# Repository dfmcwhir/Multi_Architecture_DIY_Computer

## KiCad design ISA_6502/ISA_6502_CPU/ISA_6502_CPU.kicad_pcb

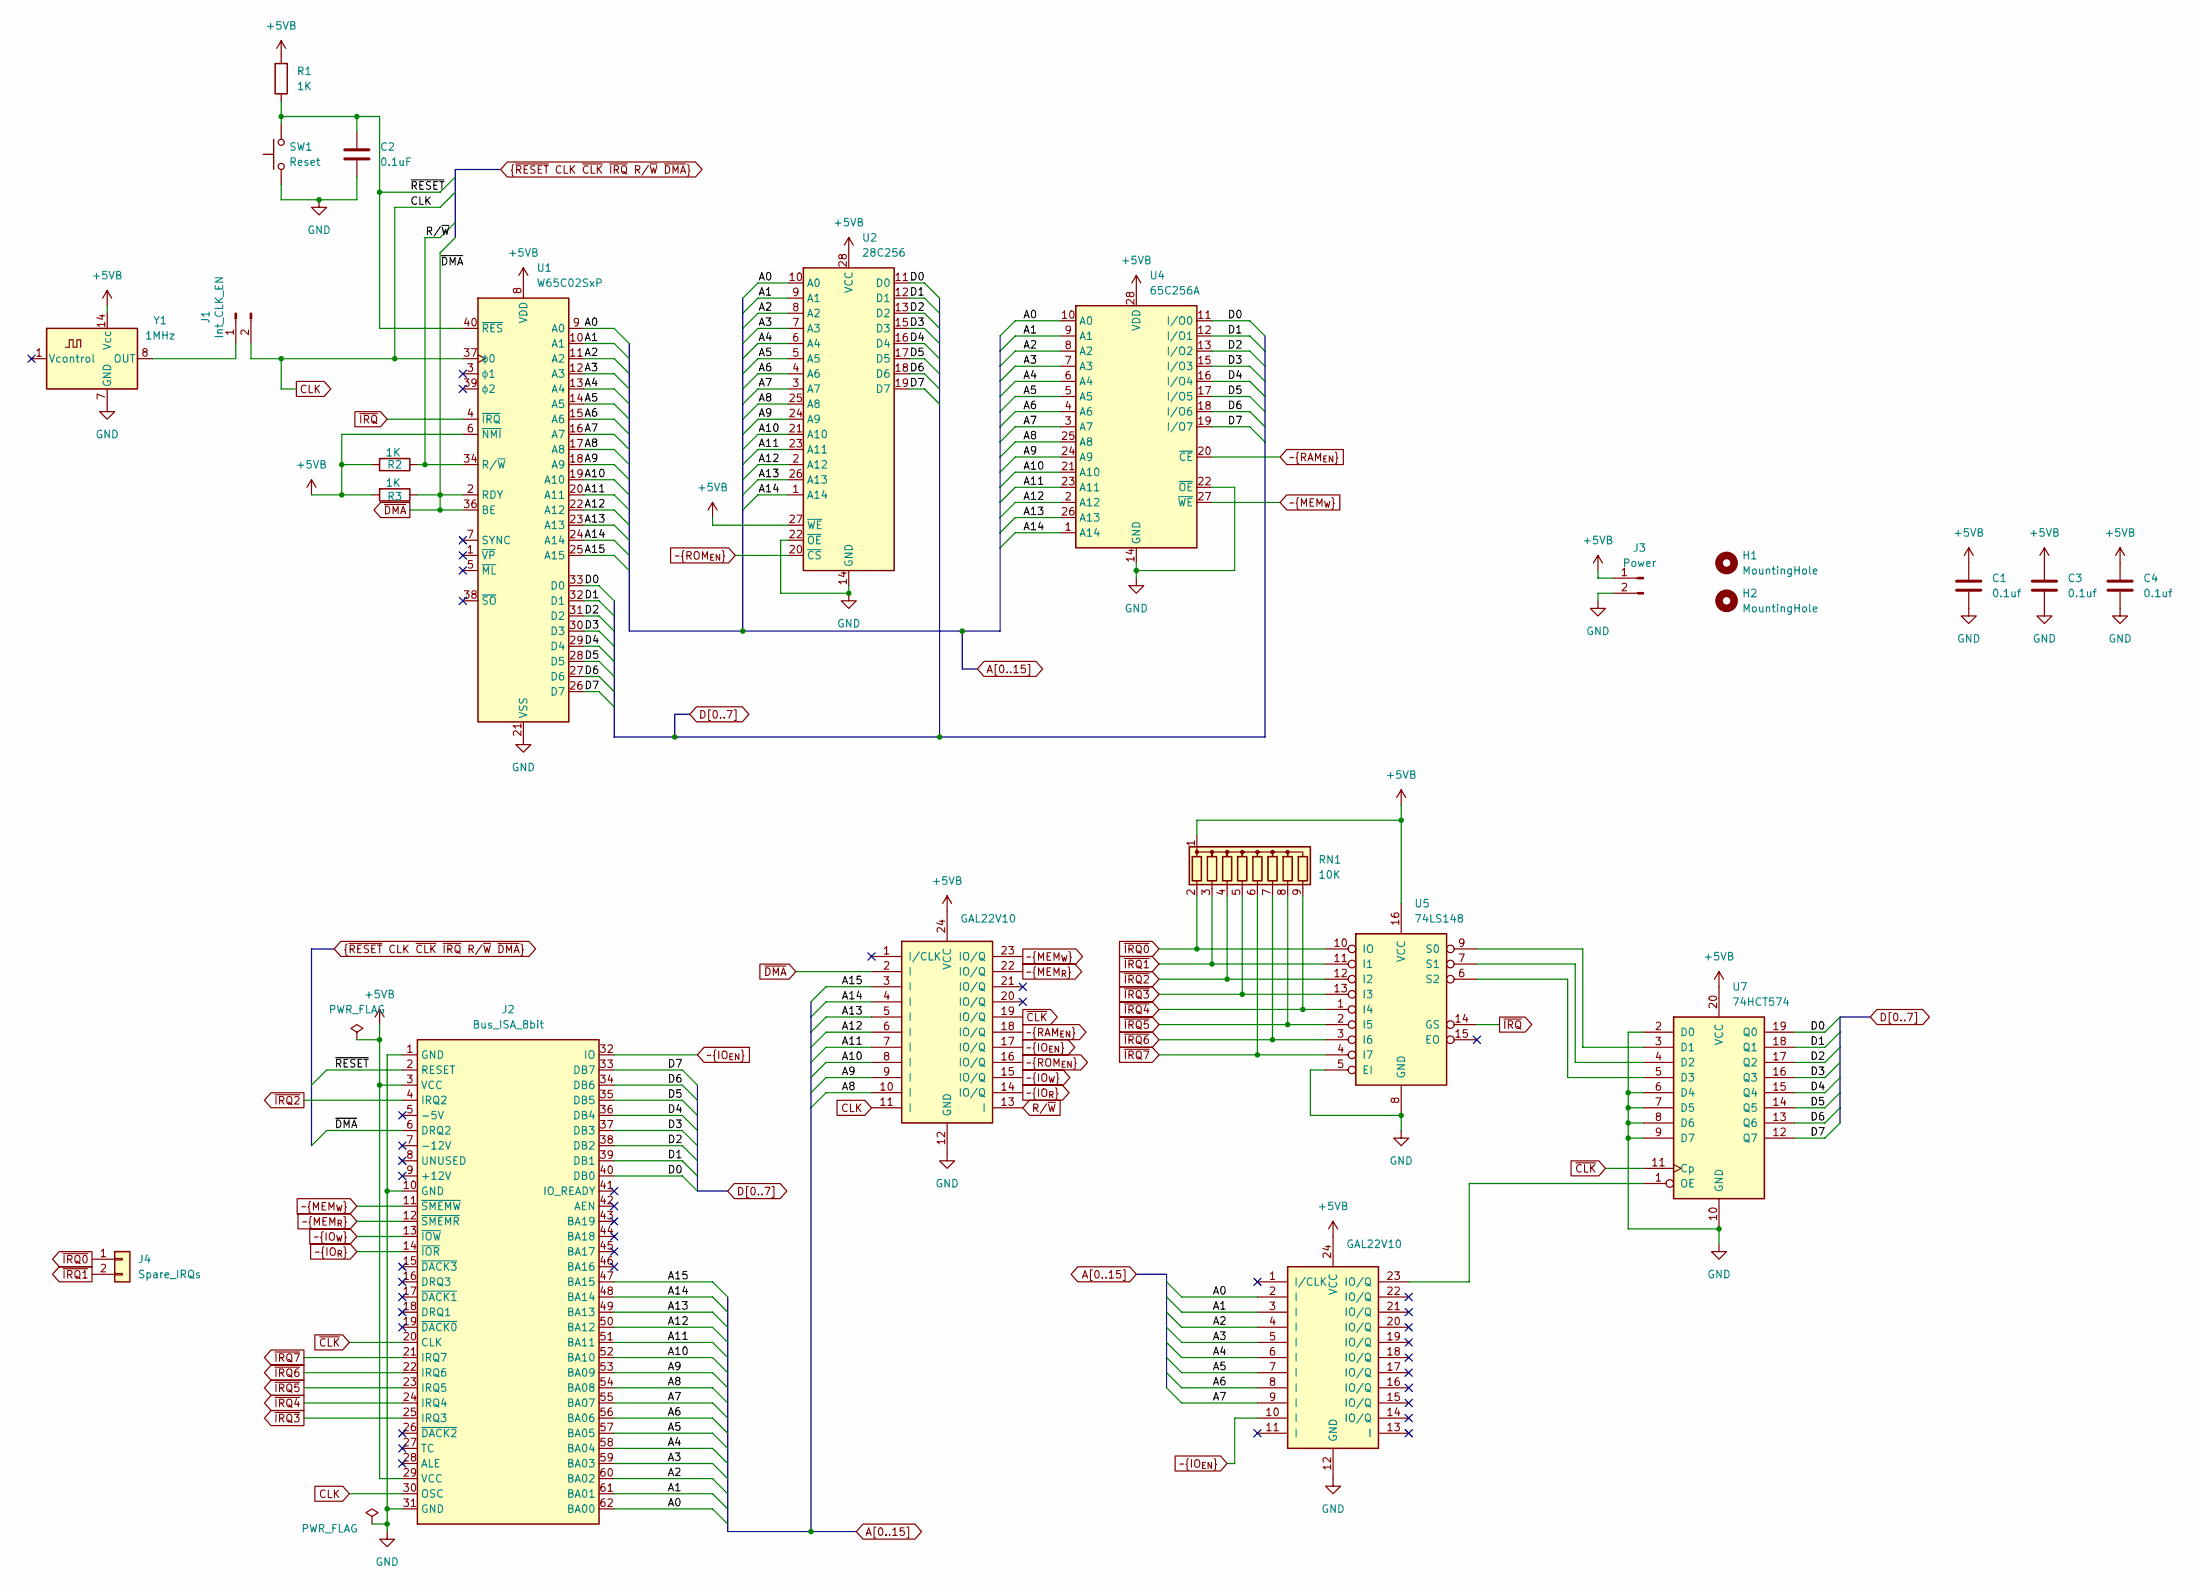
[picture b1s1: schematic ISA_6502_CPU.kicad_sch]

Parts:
C1, C3, C4: 0.1uf; C_Disc_D4.7mm_W2.5mm_P5.00mm
C2: 0.1uF; C_Disc_D4.7mm_W2.5mm_P5.00mm
H1, H2: MountingHole; MountingHole_3.2mm_M3
J1: Int_CLK_EN; PinHeader_1x02_P2.54mm_Vertical
J2: Bus_ISA_8bit; BUS_8-bit_ISA
J3: Power; PinHeader_1x02_P2.54mm_Vertical
J4: Spare_IRQs; PinHeader_1x02_P2.54mm_Vertical
R1, R2, R3: 1K; R_Axial_DIN0207_L6.3mm_D2.5mm_P10.16mm_Horizontal
RN1: 10K; R_Array_SIP9
SW1: Reset; SW_PUSH_6mm
U1: W65C02SxP; DIP-40_W15.24mm
U2: 28C256; DIP-28_W15.24mm
U3, U6: GAL22V10; DIP-24_W7.62mm
U4: 65C256A; DIP-28_W15.24mm
U5: 74LS148; DIP-16_W7.62mm
U7: 74HCT574; DIP-20_W7.62mm
Y1: 1MHz; Oscillator_DIP-14

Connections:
+5VB: C1.1, C3.1, C4.1, J2.3 (VCC), J2.29 (VCC), J3.1, R1.2, R2.2, R3.2, RN1.1 (common), U1.6 (~NMI), U1.8 (VDD), U2.27 (~WE), U2.28 (VCC), U3.24 (VCC), U4.28 (VDD), U5.16 (VCC), U6.24 (VCC), U7.20 (VCC), Y1.14 (Vcc)
A0: J2.62 (BA00), U1.9 (A0), U2.10 (A0), U4.10 (A0), U6.2 (I)
A1: J2.61 (BA01), U1.10 (A1), U2.9 (A1), U4.9 (A1), U6.3 (I)
A2: J2.60 (BA02), U1.11 (A2), U2.8 (A2), U4.8 (A2), U6.4 (I)
A3: J2.59 (BA03), U1.12 (A3), U2.7 (A3), U4.7 (A3), U6.5 (I)
A4: J2.58 (BA04), U1.13 (A4), U2.6 (A4), U4.6 (A4), U6.6 (I)
A5: J2.57 (BA05), U1.14 (A5), U2.5 (A5), U4.5 (A5), U6.7 (I)
A6: J2.56 (BA06), U1.15 (A6), U2.4 (A6), U4.4 (A6), U6.8 (I)
A7: J2.55 (BA07), U1.16 (A7), U2.3 (A7), U4.3 (A7), U6.9 (I)
A8: J2.54 (BA08), U1.17 (A8), U2.25 (A8), U3.10 (I), U4.25 (A8)
A9: J2.53 (BA09), U1.18 (A9), U2.24 (A9), U3.9 (I), U4.24 (A9)
A10: J2.52 (BA10), U1.19 (A10), U2.21 (A10), U3.8 (I), U4.21 (A10)
A11: J2.51 (BA11), U1.20 (A11), U2.23 (A11), U3.7 (I), U4.23 (A11)
A12: J2.50 (BA12), U1.22 (A12), U2.2 (A12), U3.6 (I), U4.2 (A12)
A13: J2.49 (BA13), U1.23 (A13), U2.26 (A13), U3.5 (I), U4.26 (A13)
A14: J2.48 (BA14), U1.24 (A14), U2.1 (A14), U3.4 (I), U4.1 (A14)
A15: J2.47 (BA15), U1.25 (A15), U3.3 (I)
CLK: J1.2, J2.30 (OSC), U1.37 (ϕ0), U3.11 (I)
D0: J2.40 (DB0), U1.33 (D0), U2.11 (D0), U4.11 (I/O0), U7.19 (Q0)
D1: J2.39 (DB1), U1.32 (D1), U2.12 (D1), U4.12 (I/O1), U7.18 (Q1)
D2: J2.38 (DB2), U1.31 (D2), U2.13 (D2), U4.13 (I/O2), U7.17 (Q2)
D3: J2.37 (DB3), U1.30 (D3), U2.15 (D3), U4.15 (I/O3), U7.16 (Q3)
D4: J2.36 (DB4), U1.29 (D4), U2.16 (D4), U4.16 (I/O4), U7.15 (Q4)
D5: J2.35 (DB5), U1.28 (D5), U2.17 (D5), U4.17 (I/O5), U7.14 (Q5)
D6: J2.34 (DB6), U1.27 (D6), U2.18 (D6), U4.18 (I/O6), U7.13 (Q6)
D7: J2.33 (DB7), U1.26 (D7), U2.19 (D7), U4.19 (I/O7), U7.12 (Q7)
GND: C1.2, C2.2, C3.2, C4.2, J2.1 (GND), J2.10 (GND), J2.31 (GND), J3.2, SW1.1, U1.21 (VSS), U2.14 (GND), U2.22 (~OE), U3.12 (GND), U4.14 (GND), U4.22 (~OE), U5.5 (EI), U5.8 (GND), U6.12 (GND), U7.2 (D0), U7.6 (D4), U7.7 (D5), U7.8 (D6), U7.9 (D7), U7.10 (GND), Y1.7 (GND)
unnamed: J1.1, Y1.8 (OUT)
unnamed: U5.9 (S0), U7.3 (D1)
unnamed: U5.7 (S1), U7.4 (D2)
unnamed: U5.6 (S2), U7.5 (D3)
unnamed: U6.23 (IO/Q), U7.1 (OE)
R/~W: R2.1, U1.34 (R/~W), U3.13 (I)
~CLK: J2.20 (CLK), U3.19 (IO/Q), U7.11 (Cp)
~DMA: J2.6 (DRQ2), R3.1, U1.2 (RDY), U1.36 (BE), U3.2 (I)
~IO_{EN}: J2.32 (IO), U3.17 (IO/Q), U6.10 (I)
~IO_{R}: J2.14 (~IOR), U3.14 (IO/Q)
~IO_{W}: J2.13 (~IOW), U3.15 (IO/Q)
~IRQ0: J4.1, RN1.2 (R1), U5.10 (IO)
~IRQ1: J4.2, RN1.3 (R2), U5.11 (I1)
~IRQ2: J2.4 (IRQ2), RN1.4 (R3), U5.12 (I2)
~IRQ3: J2.25 (IRQ3), RN1.5 (R4), U5.13 (I3)
~IRQ4: J2.24 (IRQ4), RN1.9 (R8), U5.1 (I4)
~IRQ5: J2.23 (IRQ5), RN1.8 (R7), U5.2 (I5)
~IRQ6: J2.22 (IRQ6), RN1.7 (R6), U5.3 (I6)
~IRQ7: J2.21 (IRQ7), RN1.6 (R5), U5.4 (I7)
~IRQ: U1.4 (~IRQ), U5.14 (GS)
~MEM_{R}: J2.12 (~SMEMR), U3.22 (IO/Q)
~MEM_{W}: J2.11 (~SMEMW), U3.23 (IO/Q), U4.27 (~WE)
~RAM_{EN}: U3.18 (IO/Q), U4.20 (~CE)
~RESET: C2.1, J2.2 (RESET), R1.1, SW1.2, U1.40 (~RES)
~ROM_{EN}: U2.20 (~CS), U3.16 (IO/Q)

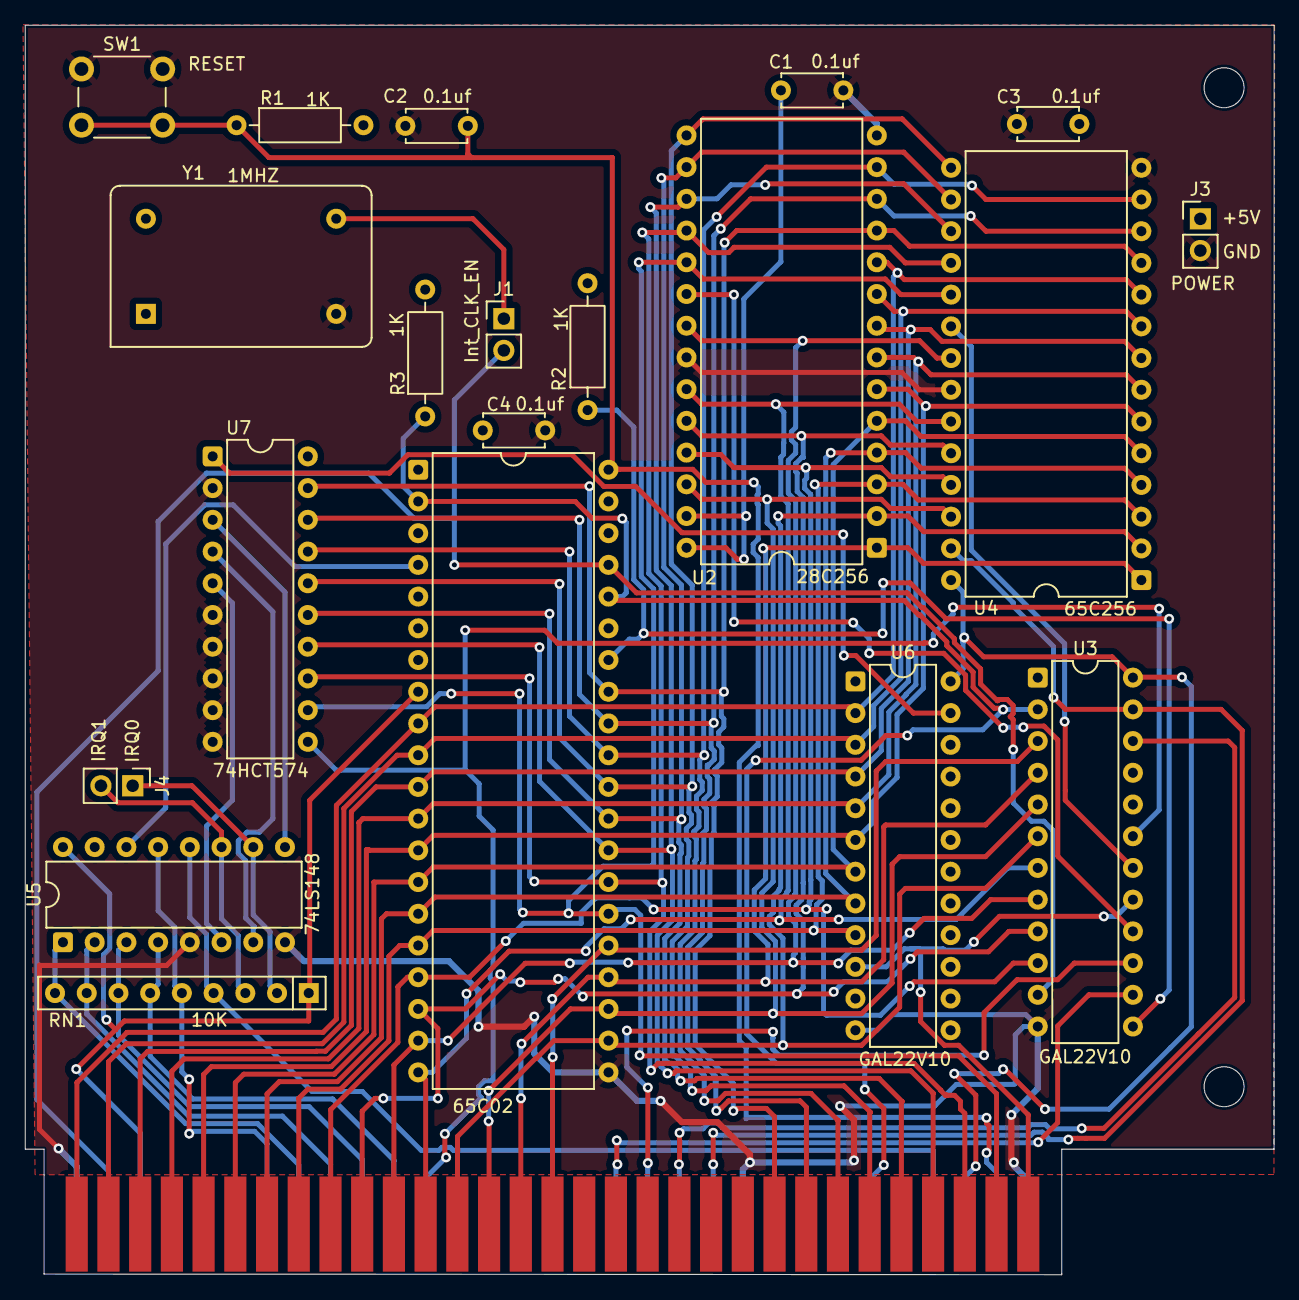
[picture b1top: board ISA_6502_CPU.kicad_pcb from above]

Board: 2 copper layers, 100.0 x 100.1 mm, 23 parts (0 on the bottom side), 52 nets.

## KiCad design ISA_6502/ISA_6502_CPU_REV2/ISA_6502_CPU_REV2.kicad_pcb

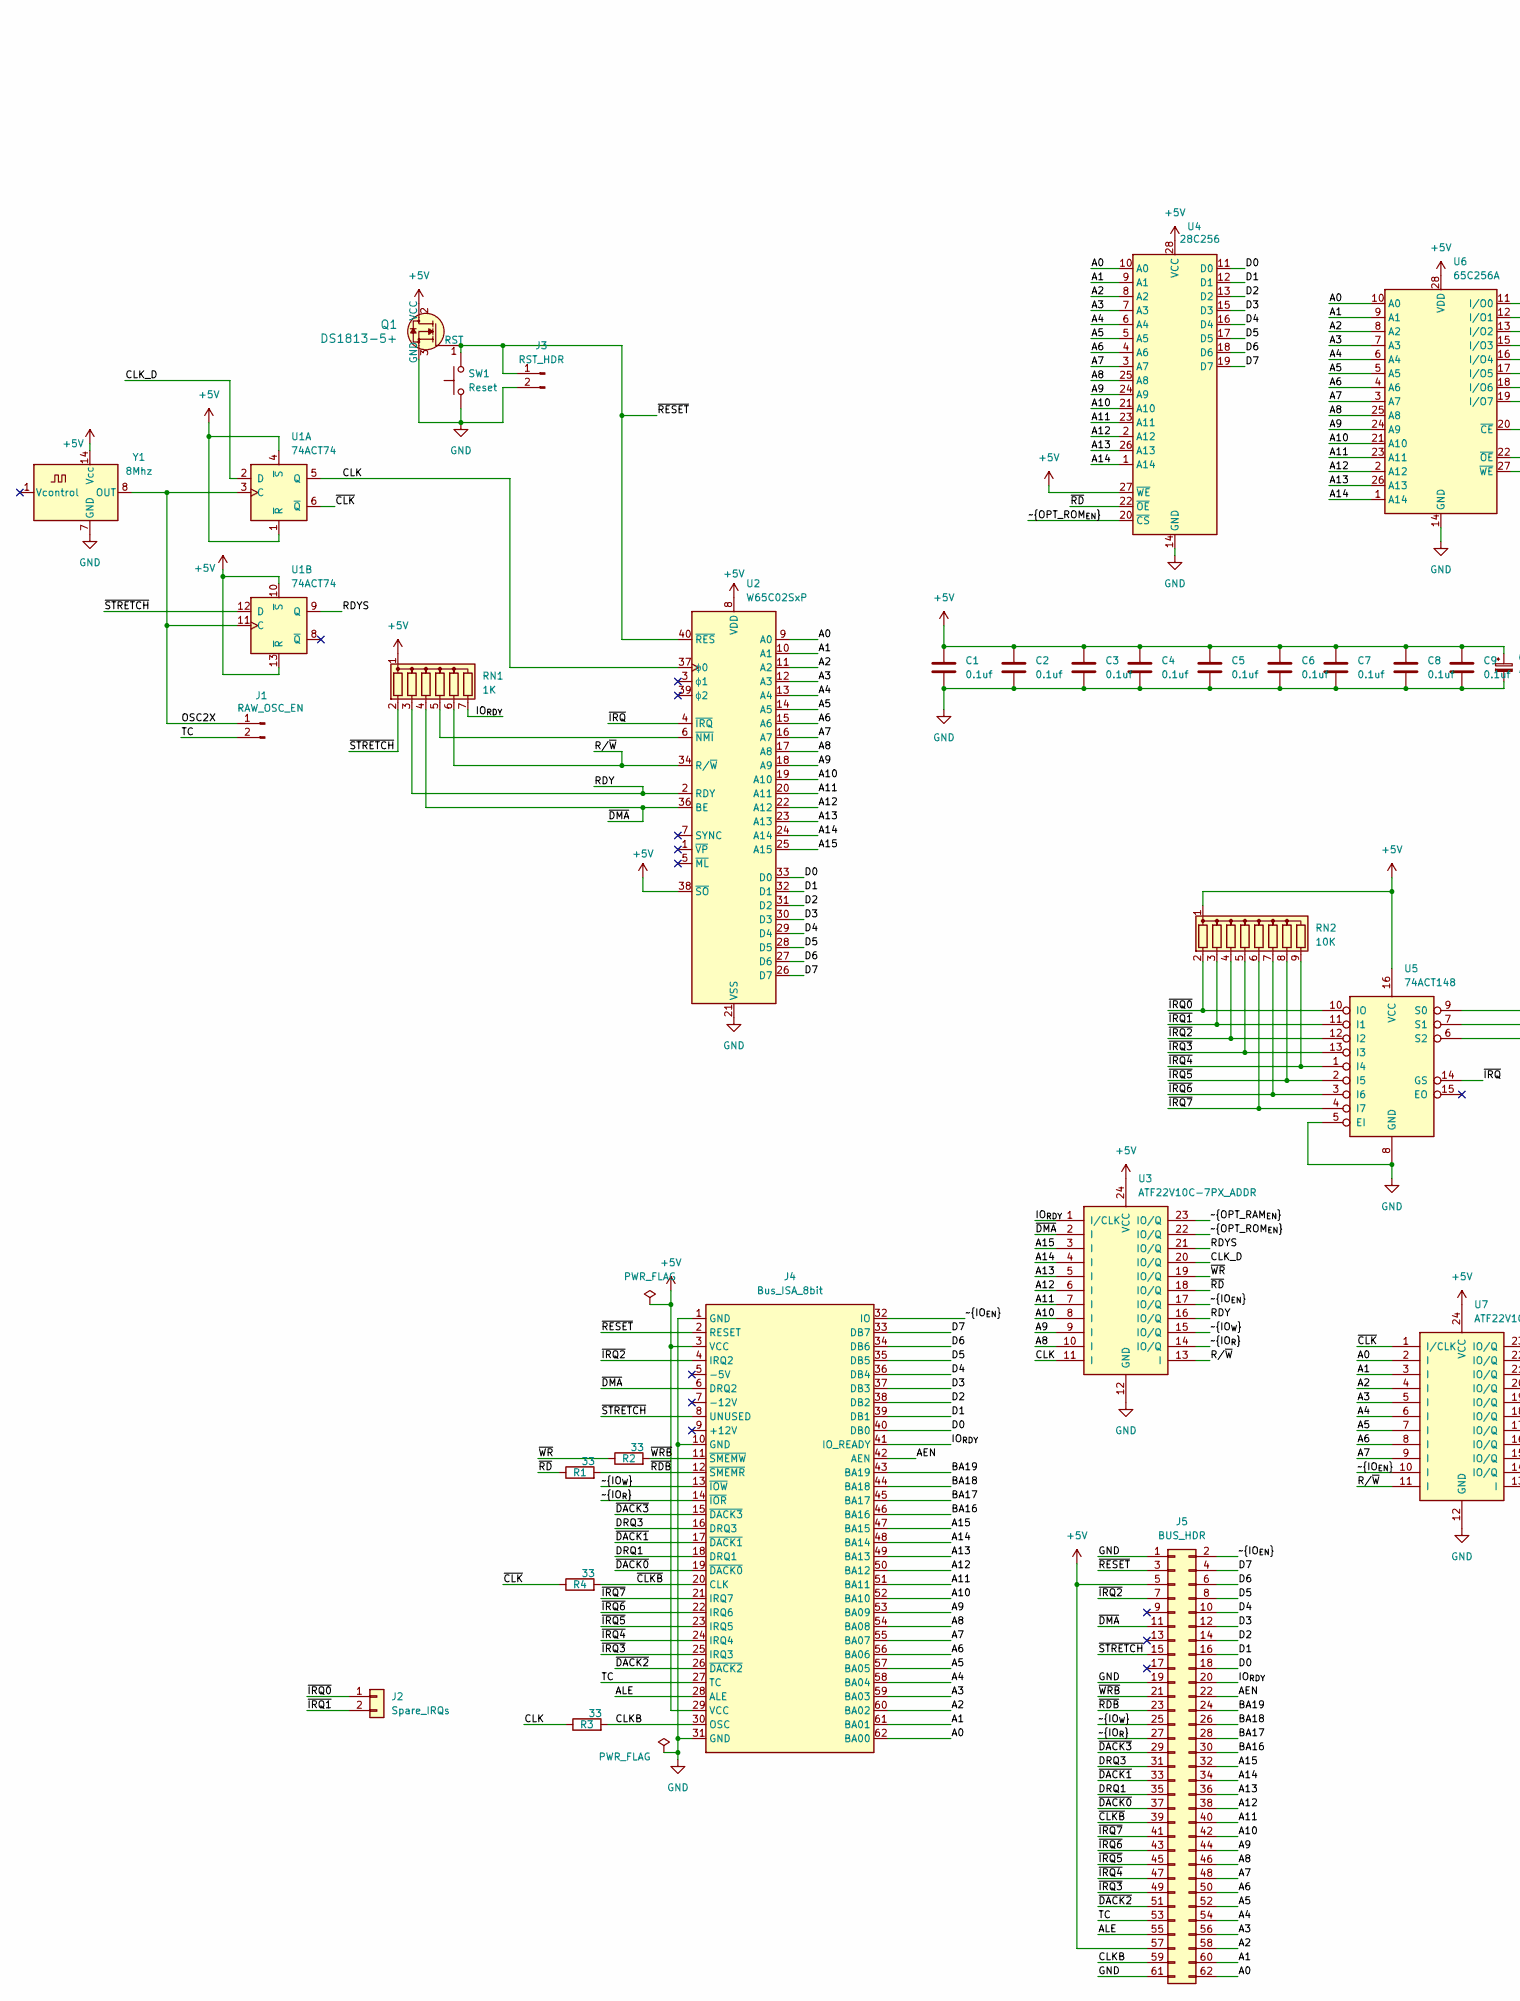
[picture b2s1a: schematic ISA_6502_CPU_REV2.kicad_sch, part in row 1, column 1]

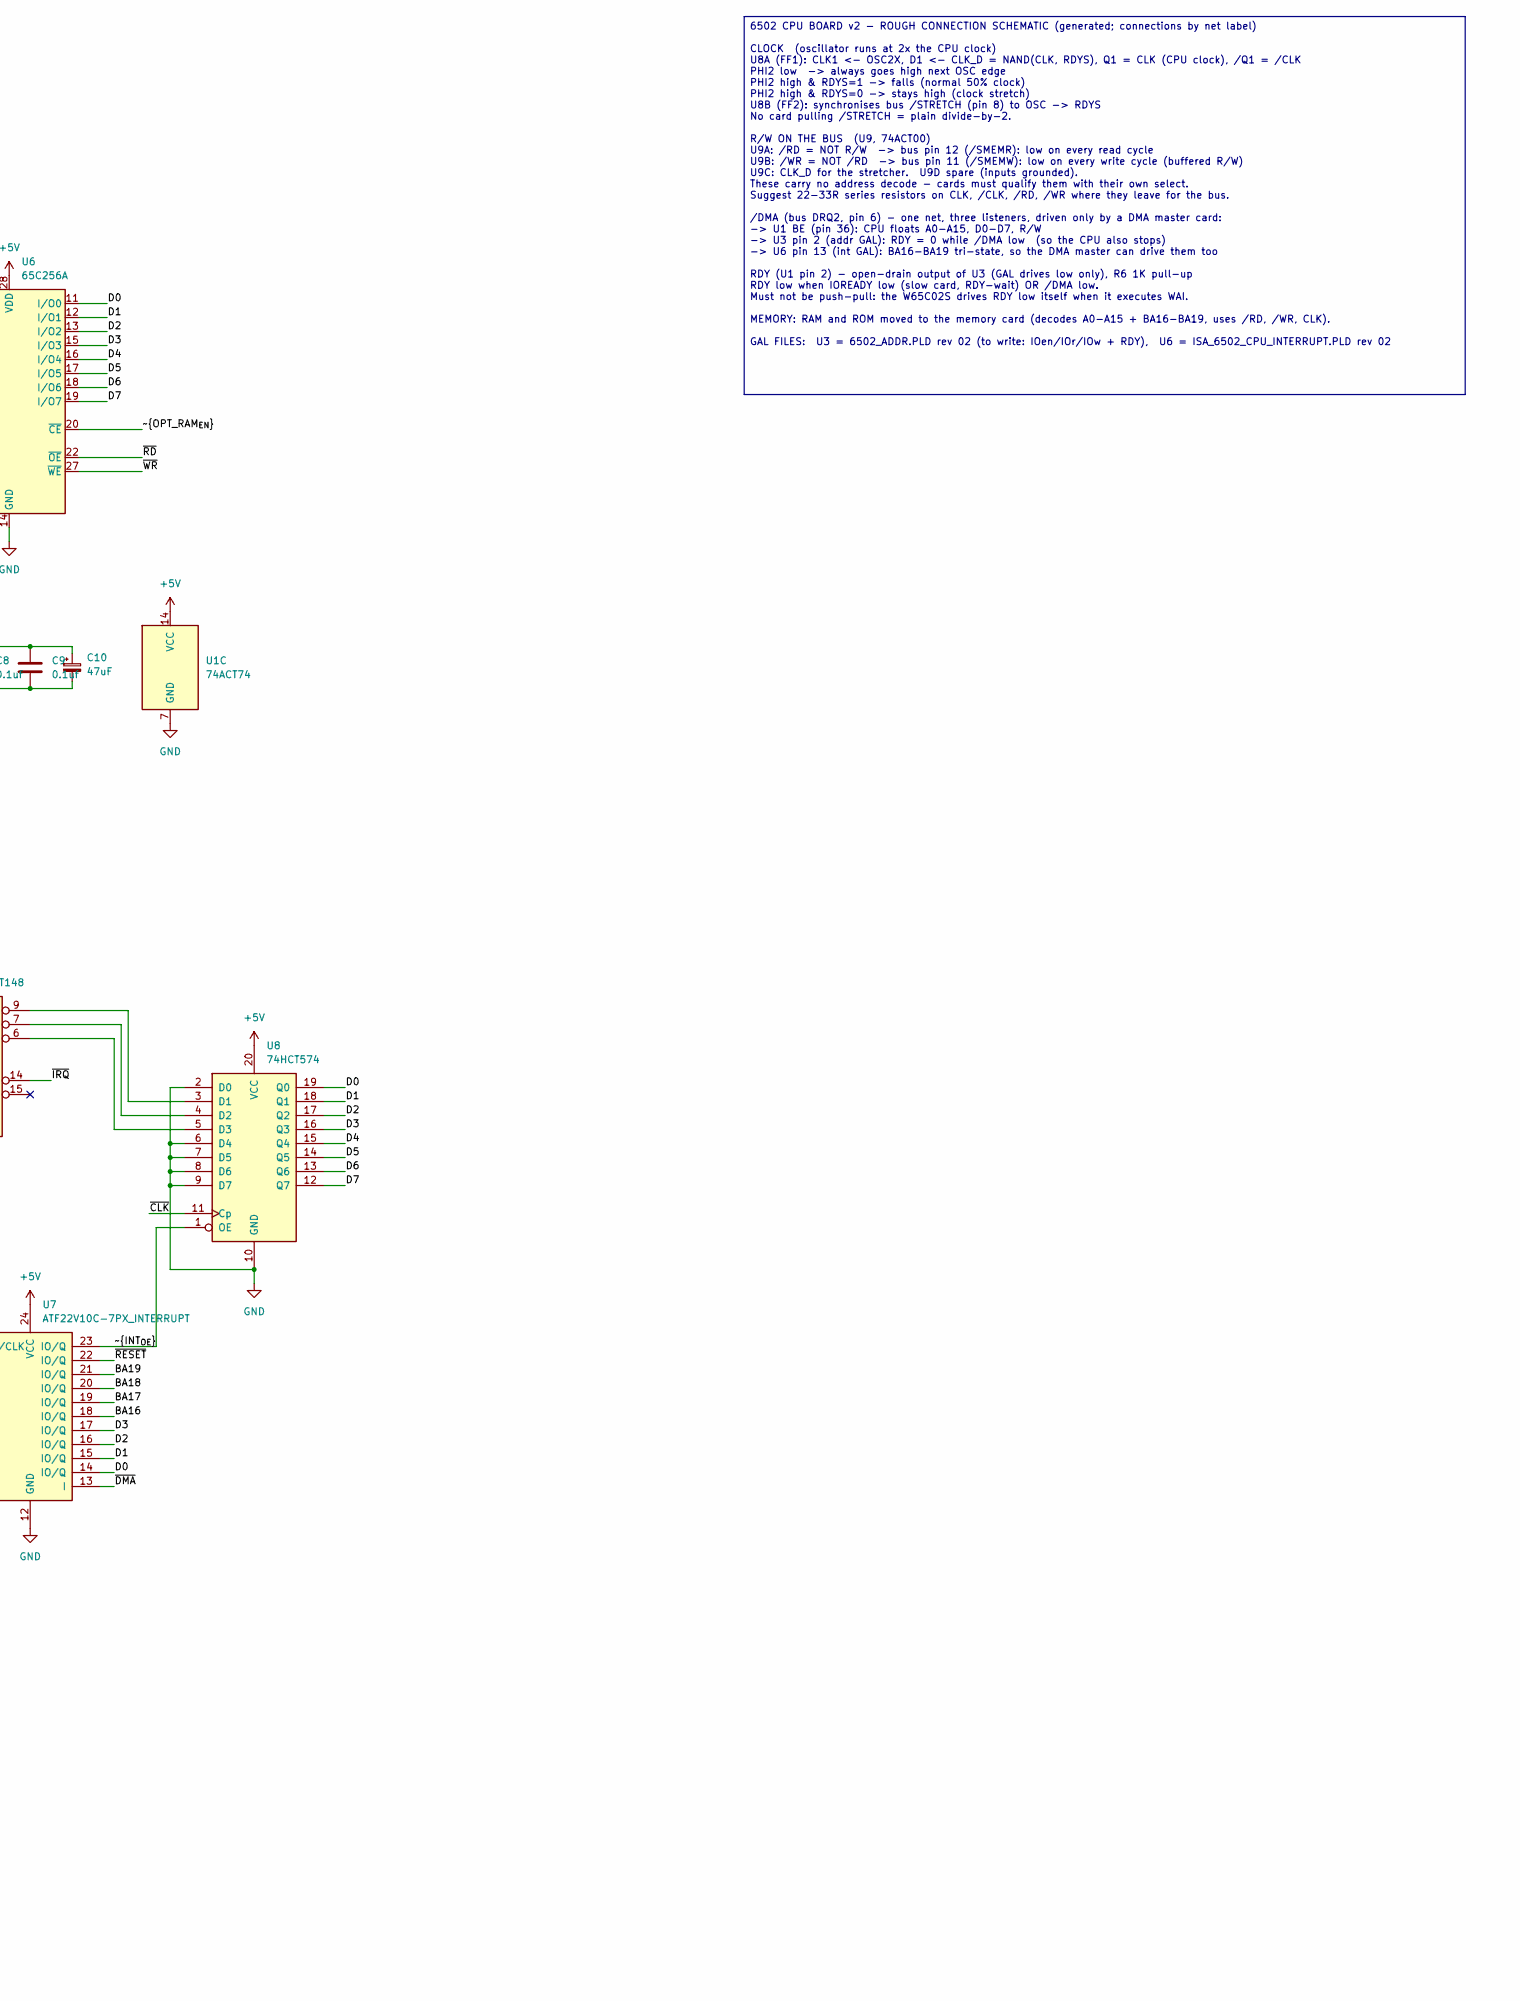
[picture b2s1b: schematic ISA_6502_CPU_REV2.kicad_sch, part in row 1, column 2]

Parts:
C1, C2, C3, C4, C5, C6, C7, C8, C9: 0.1uf; C_Disc_D4.7mm_W2.5mm_P5.00mm
C10: 47uF; CP_Radial_D5.0mm_P2.00mm
J1: RAW_OSC_EN; PinHeader_1x02_P2.54mm_Vertical
J2: Spare_IRQs; PinHeader_1x02_P2.54mm_Vertical
J3: RST_HDR; PinHeader_1x02_P2.54mm_Vertical
J4: Bus_ISA_8bit; BUS_8-bit_ISA
J5: BUS_HDR; PinHeader_2x31_P2.54mm_Vertical
Q1: DS1813-5+; TO-92L_Wide; MPN DS1813-5+-ND; Digi-Key_PN DS1813-5+-ND
R1, R2, R3, R4: 33; R_Axial_DIN0207_L6.3mm_D2.5mm_P10.16mm_Horizontal
RN1: 1K; R_Array_SIP7
RN2: 10K; R_Array_SIP9
SW1: Reset; SW_PUSH_6mm
U1: 74ACT74; DIP-14_W7.62mm
U2: W65C02SxP; DIP-40_W15.24mm
U3: ATF22V10C-7PX_ADDR; DIP-24_W7.62mm
U4: 28C256; DIP-28_W15.24mm
U5: 74ACT148; DIP-16_W7.62mm
U6: 65C256A; DIP-28_W15.24mm
U7: ATF22V10C-7PX_INTERRUPT; DIP-24_W7.62mm
U8: 74HCT574; DIP-20_W7.62mm
Y1: 8Mhz; Oscillator_DIP-14

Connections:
+5V: C1.1, C2.1, C3.1, C4.1, C5.1, C6.1, C7.1, C8.1, C9.1, C10.1, J4.3 (VCC), J4.29 (VCC), J5.5, J5.57, Q1.2 (VCC), RN1.1 (common), RN2.1 (common), U1.1 (~R), U1.4 (~S), U1.10 (~S), U1.13 (~R), U1.14 (VCC), U2.8 (VDD), U2.38 (~SO), U3.24 (VCC), U4.27 (~WE), U4.28 (VCC), U5.16 (VCC), U6.28 (VDD), U7.24 (VCC), U8.20 (VCC), Y1.14 (Vcc)
/A0: J4.62 (BA00), J5.62, U2.9 (A0), U4.10 (A0), U6.10 (A0), U7.2 (I)
/A1: J4.61 (BA01), J5.60, U2.10 (A1), U4.9 (A1), U6.9 (A1), U7.3 (I)
/A2: J4.60 (BA02), J5.58, U2.11 (A2), U4.8 (A2), U6.8 (A2), U7.4 (I)
/A3: J4.59 (BA03), J5.56, U2.12 (A3), U4.7 (A3), U6.7 (A3), U7.5 (I)
/A4: J4.58 (BA04), J5.54, U2.13 (A4), U4.6 (A4), U6.6 (A4), U7.6 (I)
/A5: J4.57 (BA05), J5.52, U2.14 (A5), U4.5 (A5), U6.5 (A5), U7.7 (I)
/A6: J4.56 (BA06), J5.50, U2.15 (A6), U4.4 (A6), U6.4 (A6), U7.8 (I)
/A7: J4.55 (BA07), J5.48, U2.16 (A7), U4.3 (A7), U6.3 (A7), U7.9 (I)
/A8: J4.54 (BA08), J5.46, U2.17 (A8), U3.10 (I), U4.25 (A8), U6.25 (A8)
/A9: J4.53 (BA09), J5.44, U2.18 (A9), U3.9 (I), U4.24 (A9), U6.24 (A9)
/A10: J4.52 (BA10), J5.42, U2.19 (A10), U3.8 (I), U4.21 (A10), U6.21 (A10)
/A11: J4.51 (BA11), J5.40, U2.20 (A11), U3.7 (I), U4.23 (A11), U6.23 (A11)
/A12: J4.50 (BA12), J5.38, U2.22 (A12), U3.6 (I), U4.2 (A12), U6.2 (A12)
/A13: J4.49 (BA13), J5.36, U2.23 (A13), U3.5 (I), U4.26 (A13), U6.26 (A13)
/A14: J4.48 (BA14), J5.34, U2.24 (A14), U3.4 (I), U4.1 (A14), U6.1 (A14)
/A15: J4.47 (BA15), J5.32, U2.25 (A15), U3.3 (I)
/AEN: J4.42 (AEN), J5.22
/ALE: J4.28 (ALE), J5.55
/BA16: J4.46 (BA16), J5.30, U7.18 (IO/Q)
/BA17: J4.45 (BA17), J5.28, U7.19 (IO/Q)
/BA18: J4.44 (BA18), J5.26, U7.20 (IO/Q)
/BA19: J4.43 (BA19), J5.24, U7.21 (IO/Q)
/CLK: R3.1, U1.5 (Q), U2.37 (ϕ0), U3.11 (I)
/CLKB: J4.30 (OSC), J5.59, R3.2
/CLK_D: U1.2 (D), U3.20 (IO/Q)
/D0: J4.40 (DB0), J5.18, U2.33 (D0), U4.11 (D0), U6.11 (I/O0), U7.14 (IO/Q), U8.19 (Q0)
/D1: J4.39 (DB1), J5.16, U2.32 (D1), U4.12 (D1), U6.12 (I/O1), U7.15 (IO/Q), U8.18 (Q1)
/D2: J4.38 (DB2), J5.14, U2.31 (D2), U4.13 (D2), U6.13 (I/O2), U7.16 (IO/Q), U8.17 (Q2)
/D3: J4.37 (DB3), J5.12, U2.30 (D3), U4.15 (D3), U6.15 (I/O3), U7.17 (IO/Q), U8.16 (Q3)
/D4: J4.36 (DB4), J5.10, U2.29 (D4), U4.16 (D4), U6.16 (I/O4), U8.15 (Q4)
/D5: J4.35 (DB5), J5.8, U2.28 (D5), U4.17 (D5), U6.17 (I/O5), U8.14 (Q5)
/D6: J4.34 (DB6), J5.6, U2.27 (D6), U4.18 (D6), U6.18 (I/O6), U8.13 (Q6)
/D7: J4.33 (DB7), J5.4, U2.26 (D7), U4.19 (D7), U6.19 (I/O7), U8.12 (Q7)
/DRQ1: J4.18 (DRQ1), J5.35
/DRQ3: J4.16 (DRQ3), J5.31
/IO_{RDY}: J4.41 (IO_READY), J5.20, RN1.7 (R6), U3.1 (I/CLK)
/OSC2X: J1.1, U1.3 (C), U1.11 (C), Y1.8 (OUT)
/RDY: RN1.3 (R2), U2.2 (RDY), U3.16 (IO/Q)
/RDYS: U1.9 (Q), U3.21 (IO/Q)
/R/~W: RN1.6 (R5), U2.34 (R/~W), U3.13 (I), U7.11 (I)
/TC: J1.2, J4.27 (TC), J5.53
/~CLKB: J4.20 (CLK), J5.39, R4.2
/~CLK: R4.1, U1.6 (~Q), U7.1 (I/CLK), U8.11 (Cp)
/~DACK0: J4.19 (~DACK0), J5.37
/~DACK1: J4.17 (~DACK1), J5.33
/~DACK2: J4.26 (~DACK2), J5.51
/~DACK3: J4.15 (~DACK3), J5.29
/~DMA: J4.6 (DRQ2), J5.11, RN1.4 (R3), U2.36 (BE), U3.2 (I), U7.13 (I)
/~INT_{OE}: U7.23 (IO/Q), U8.1 (OE)
/~IO_{EN}: J4.32 (IO), J5.2, U3.17 (IO/Q), U7.10 (I)
/~IO_{R}: J4.14 (~IOR), J5.27, U3.14 (IO/Q)
/~IO_{W}: J4.13 (~IOW), J5.25, U3.15 (IO/Q)
/~IRQ0: J2.1, RN2.2 (R1), U5.10 (IO)
/~IRQ1: J2.2, RN2.3 (R2), U5.11 (I1)
/~IRQ2: J4.4 (IRQ2), J5.7, RN2.4 (R3), U5.12 (I2)
/~IRQ3: J4.25 (IRQ3), J5.49, RN2.5 (R4), U5.13 (I3)
/~IRQ4: J4.24 (IRQ4), J5.47, RN2.9 (R8), U5.1 (I4)
/~IRQ5: J4.23 (IRQ5), J5.45, RN2.8 (R7), U5.2 (I5)
/~IRQ6: J4.22 (IRQ6), J5.43, RN2.7 (R6), U5.3 (I6)
/~IRQ7: J4.21 (IRQ7), J5.41, RN2.6 (R5), U5.4 (I7)
/~IRQ: U2.4 (~IRQ), U5.14 (GS)
/~OPT_RAM_{EN}: U3.23 (IO/Q), U6.20 (~CE)
/~OPT_ROM_{EN}: U3.22 (IO/Q), U4.20 (~CS)
/~RDB: J4.12 (~SMEMR), J5.23, R1.2
/~RD: R1.1, U3.18 (IO/Q), U4.22 (~OE), U6.22 (~OE)
/~RESET: J3.1, J4.2 (RESET), J5.3, Q1.1 (RST), SW1.2, U2.40 (~RES), U7.22 (IO/Q)
/~STRETCH: J4.8 (UNUSED), J5.15, RN1.2 (R1), U1.12 (D)
/~WRB: J4.11 (~SMEMW), J5.21, R2.2
/~WR: R2.1, U3.19 (IO/Q), U6.27 (~WE)
GND: C1.2, C2.2, C3.2, C4.2, C5.2, C6.2, C7.2, C8.2, C9.2, C10.2, J3.2, J4.1 (GND), J4.10 (GND), J4.31 (GND), J5.1, J5.19, J5.61, Q1.3 (GND), SW1.1, U1.7 (GND), U2.21 (VSS), U3.12 (GND), U4.14 (GND), U5.5 (EI), U5.8 (GND), U6.14 (GND), U7.12 (GND), U8.2 (D0), U8.6 (D4), U8.7 (D5), U8.8 (D6), U8.9 (D7), U8.10 (GND), Y1.7 (GND)
unnamed: RN1.5 (R4), U2.6 (~NMI)
unnamed: U5.9 (S0), U8.3 (D1)
unnamed: U5.7 (S1), U8.4 (D2)
unnamed: U5.6 (S2), U8.5 (D3)

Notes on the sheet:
6502 CPU BOARD v2 - ROUGH CONNECTION SCHEMATIC (generated; connections by net label) CLOCK (oscillator runs at 2x the CPU clock) U8A (FF1): CLK1 <- OSC2X, D1 <- CLK_D = NAND(CLK, RDYS), Q1 = CLK (CPU clock), /Q1 = /CLK PHI2 low -> always goes high next OSC edge PHI2 high & RDYS=1 -> falls (normal 5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

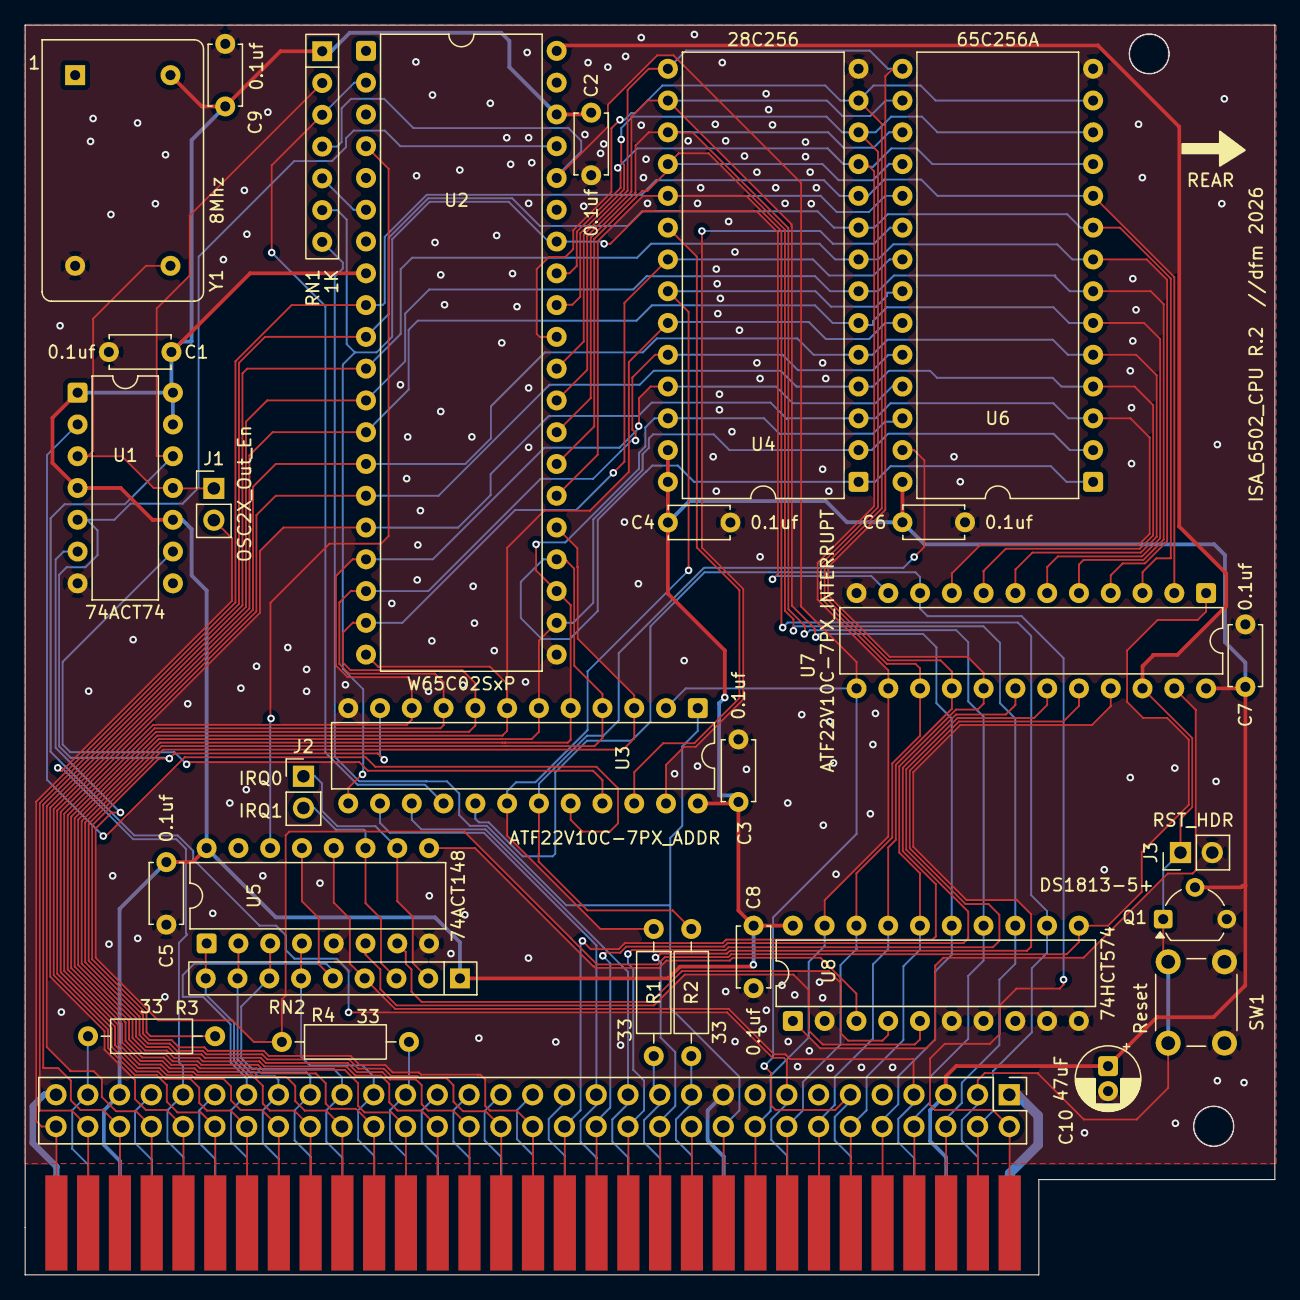
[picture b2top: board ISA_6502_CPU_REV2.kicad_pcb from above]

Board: 2 copper layers, 99.9 x 99.9 mm, 32 parts (0 on the bottom side), 75 nets.
